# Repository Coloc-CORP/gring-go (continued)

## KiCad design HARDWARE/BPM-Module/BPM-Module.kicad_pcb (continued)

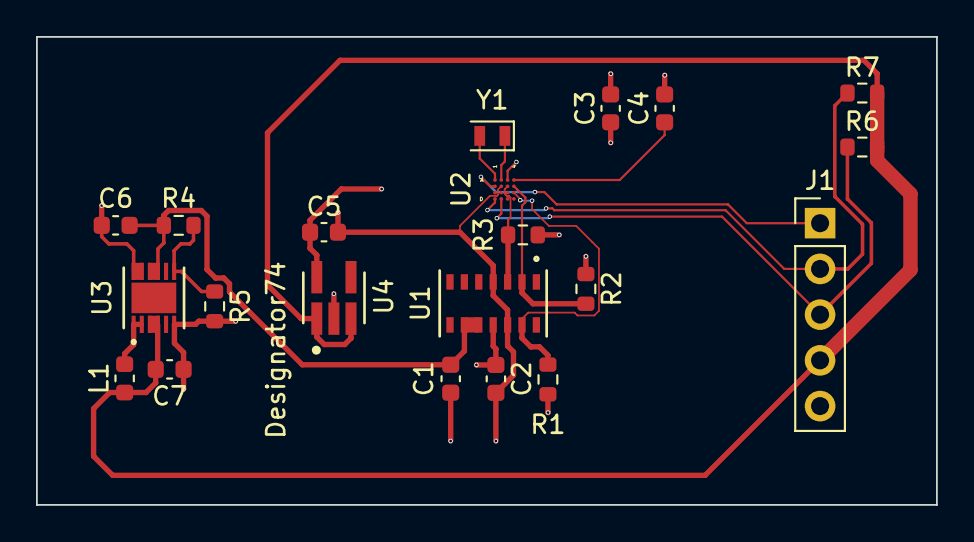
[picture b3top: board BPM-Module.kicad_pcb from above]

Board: 2 copper layers, 50.0 x 26.0 mm, 21 parts (0 on the bottom side), 15 nets.

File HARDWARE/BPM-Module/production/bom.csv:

Designator,Footprint,Quantity,Value,LCSC Part #
"C1, C7",0603,2,10u,
C2,0603,1,100n,
"C3, C4, C5",0603,3,1u,
C6,0603,1,22u,
J1,PinHeader_1x05_P2.54mm_Vertical,1,Conn_01x05_Pin,
L1,0603,1,2u2,
"R1, R2, R3, R6, R7",0603,5,4K7,
R4,0603,1,750K,
R5,0603,1,100K,
U1,21-1048_F143A5&plus_1_MXM-M,1,MAX30101EFD+,
U2,21-100241A_W161K1&plus_1_MXM,1,MAX32664GWEA+T,
U3,SON12_U-DFN3030-12_DIO-M,1,PAM2401YPADJ,
U4,DBV0005A-IPC_A,1,PTPS7A2018PDBVR,
Y1,Crystal_SMD_2012-2Pin_2.0x1.2mm,1,32k768,

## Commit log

2025-04-03 Folder creation
2025-04-03 Folder creation 2
2025-04-27 Folder Architecture changes
2025-04-27 README first version
2025-04-27 Versionning 3D models folder
2025-09-11 init android app
2025-09-23 Template for component analysis
2025-09-23 Task file and time estimation
2025-09-23 Marius' Tasks
2025-09-23 Ajout cahier des charges
2025-09-23 add gitignore
2025-09-23 Gantt creation
2025-09-23 Gantt beginning
2025-09-23 Rédaction cahier des charges V1
2025-09-23 Adding Datasheets
2025-09-23 HR and IMU sensors sections
2025-09-28 Adding permissions
2025-09-28 Add components diagram
    Adding accelero + change health sensor
2025-09-30 Bluetooth dev, add button
2025-10-06 Ajout d'un programme test
    Programme en vue de communiquer en Bluetooth avec l'application
2025-10-07 Gantt updated
2025-10-14 Adding fragment for the app
2025-12-02 Schematics and PCB for the BPM module
2025-12-02 BPM Module - DRC problems solving
2025-12-02 BPM Module - Fabrication files
2025-12-09 Update gitignore for build folders
2025-12-09 First firmware architecture diagram
2025-12-09 Safe config base for ble communication
2025-12-09 Sample code working for ble communication
2025-12-09 Create all the files from firmware architecture
2025-12-10 Update for final component choices with IMU
2025-12-10 Sensors comparison
2025-12-10 Updating the final choices table
2025-12-10 Order request document partially filled
2025-12-10 BPM Module PCB
    * Schematics and PCB for the BPM module
    * BPM Module - DRC problems solving
    * BPM Module - Fabrication files
2025-12-11 Theoric global consumption study
2025-12-11 Update documents with haptic components
2025-12-12 TableTestFootprints - 1.0
    Quelque pépins à régler en vue de faire des tests sur ce PCB.
    A voir avec Marius pour les pins utiles, haute fréquence, d'autres composants...
2025-12-12 PCB test Marius - 3 composants faits
    Potentiellement rajouter certains composants avant de le commander (je vais laisser faire MARIUS)
2025-12-14 Update the eval kit PCB with BPM module part
2025-12-14 Generate the production files
2025-12-14 Update the firmware architecture and the files
2025-12-14 FW functions prototypes document
2025-12-14 Create sensor hubs flashing binary files
2025-12-14 Defining the firmware architecture (#26)
    * Update the firmware architecture and the files
    * FW functions prototypes document
    * Create sensor hubs flashing binary files
2025-12-14 Update the CMakeLists file
2025-12-16 Revise wireless charging components in documentation
    Add marius parts (charging)
2025-12-16 Update battery entry with specific product link
    Add test batterie
2025-12-16 Update Demande-Achat.md
    Change to lipo batterie
2025-12-16 Comparison and final choices of main components
    * HR and IMU sensors sections
    * Sensors comparison
    * Updating the final choices table
    * Update for final component choices with IMU
    * Order request document partially filled
    * Theoric global consumption study
2025-12-16 Defining the different struct and enum
2025-12-16 Haptic driver functions prototypes
2025-12-16 Update the eval kit PCB and production files
2025-12-16 Update PCB and production with GND zone on front face
2025-12-18 Custom Eval boards PCB
    * TableTestFootprints - 1.0
    Quelque pépins à régler en vue de faire des tests sur ce PCB.
    A voir avec Marius pour les pins utiles, haute fréquence, d'autres composants...
    * PCB test Marius - 3 composants faits
    Potentiellement rajouter certains composants avant de le commander (je vais laisser faire MARIUS)
    * Update the eval kit PCB with BPM module part
2025-12-18 Update via diameter and hole diameter for evk PCB
2025-12-18 Refresh of the diagram and add information on hours
2025-12-19 Correction before buy JLCPCB
    Remove of via down to 2 tiny component
    Change of clearance of the pads to pass routes
    To remove clearance : select all the pads > propriétés > Clearance Overrides and DON T PUT 0 (herited) but something like -0.001
2025-12-19 Update scheme and PCB for evk boards with adapted component packages
2025-12-19 Update zones
2025-12-19 Update inductor package
2025-12-19 Update holes
2025-12-19 Update the quartz model
2025-12-23 Adding the overlay configuration file
2025-12-23 Updating haptic pattern types
2025-12-23 Implement the haptic driver code
2025-12-23 Update the prj.conf file
2025-12-23 Haptic driver implementation (#37)
    * Update the CMakeLists file
    * Defining the different struct and enum
    * Haptic driver functions prototypes
    * Adding the overlay configuration file
    * Updating haptic pattern types
    * Implement the haptic driver code
2025-12-23 Fix the evk board with the adapted component packages (#36)
    * Correction before buy JLCPCB
    Remove of via down to 2 tiny component
    Change of clearance of the pads to pass routes
    To remove clearance : select all the pads > propriétés > Clearance Overrides and DON T PUT 0 (herited) but something like -0.001
    * Update scheme and PCB for evk boards with adapted component packages
    * Update zones
2025-12-23 IMU driver implementation to test
2025-12-25 Temperature driver to test
2025-12-28 Update thanks to the review of Mathys
2026-01-05 Update overlay file with biometric sensor
2026-01-06 First version of biometric driver
2026-01-13 Charge driver implemetation (to verify)
2026-01-20 Update image path for project diagram
2026-01-20 Fix image URL in Cahier des charges.md
    Updated image source in the document and corrected the image URL for the project diagram.
2026-01-20 Remove image
2026-01-24 Ajout avancement projet
    Dans le cadre du rendu intermédiaire
2026-01-24 Ajouts retards pour rendu intermédiaires
    Modification directement dans le fichier Gantt + ajout dans l'avancement + génération pdf
2026-01-24 Ajout archive rendu intermédiaire
2026-02-03 Function prototypes update
2026-02-03 First version ofstandard GATT services
2026-02-03 Temperature driver working with some bugs
2026-04-28 Add of Kicad components libraries
2026-04-28 Add of Gringito Kicad project
2026-05-04 End schematics PCB Wireless Charge
2026-05-04 bluetooth UUIDs class
2026-05-04 AJout d'un compteur basique pour tester la communication
2026-05-04 Clean addition of the NRF test file
    Version with the basic counter
2026-05-06 V1 PCB Wireless charging
2026-05-06 V2 PCB / MODIFS DE PLAN / ERREURS
2026-05-11 final version + bom
2026-05-11 Creation of Gringo-ring Kicad project
2026-05-11 Add kicad symbol libraries
2026-05-11 corrections via pas au bon potentiel
2026-05-18 Enhance communication Bluetooth
    Mise à jour appli Android + Gestion GATT côté NRF
2026-05-18 Add of schematics pages
2026-05-21 Main test code for haptic driver
2026-05-21 Commit new organization of files on KiCAD
2026-06-12 Temporary code (not tested)
2026-06-12 Temporary main test
2026-06-12 temp
2026-06-12 Ouai .h ajout ébauche de ....et.....service GATT
2026-06-12 Simulation data sending to android app by bluetooth
2026-06-14 Handle full communication
2026-06-15 Demo prete avec ble, temp et haptic fonctionnels
2026-06-15 Enhancing of functions of the app + bug correction
